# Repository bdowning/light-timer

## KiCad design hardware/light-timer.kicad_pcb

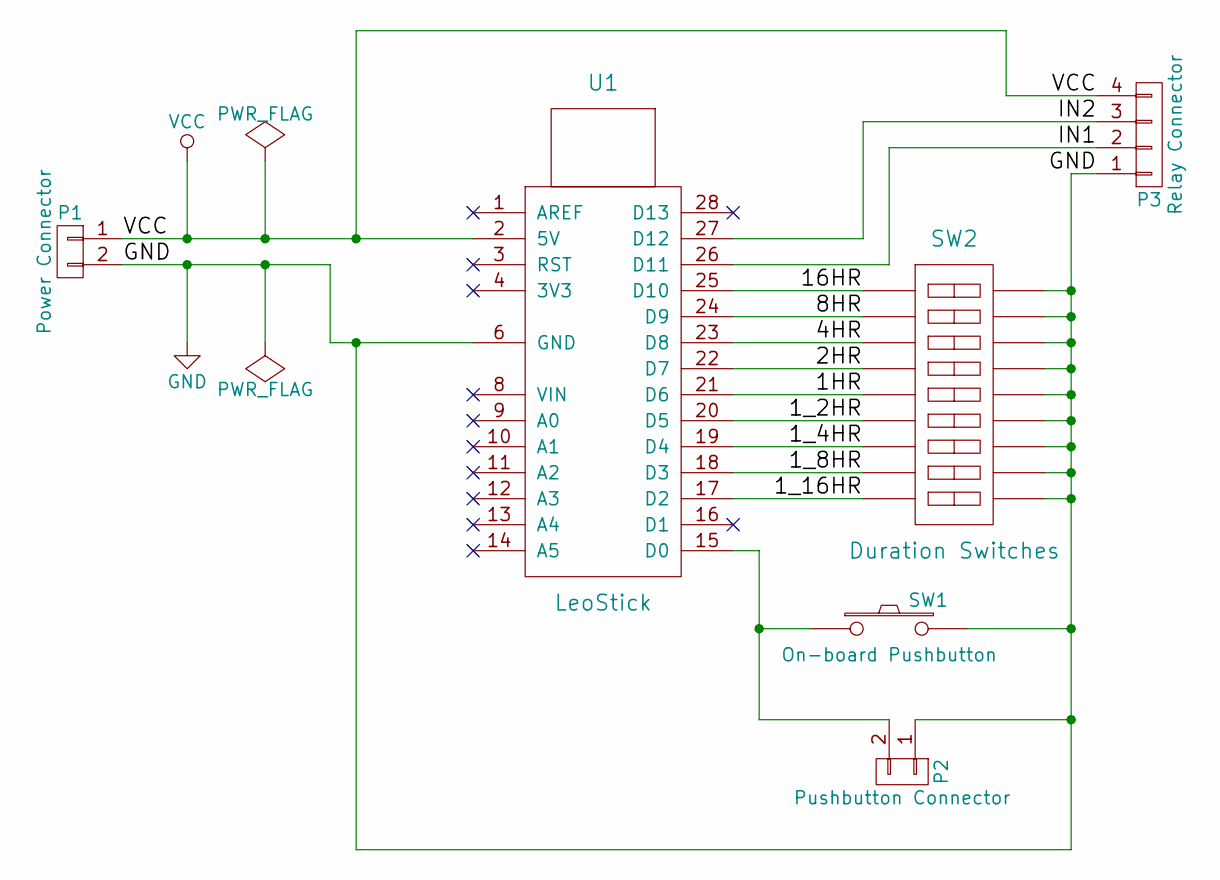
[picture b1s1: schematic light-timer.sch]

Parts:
P1: Power Connector; Socket_Strip_Straight_1x02
P2: Pushbutton Connector; Socket_Strip_Straight_1x02
P3: Relay Connector; Socket_Strip_Straight_1x04
SW1: On-board Pushbutton; SW_PUSH-12mm
SW2: Duration Switches; DIP-18_W7.62mm
U1: LeoStick; DIP-28_W15.24mm

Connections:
/1HR: SW2.5, U1.21 (D6)
/1_2HR: SW2.6, U1.20 (D5)
/1_4HR: SW2.7, U1.19 (D4)
/1_8HR: SW2.8, U1.18 (D3)
/1_16HR: SW2.9, U1.17 (D2)
/2HR: SW2.4, U1.22 (D7)
/4HR: SW2.3, U1.23 (D8)
/8HR: SW2.2, U1.24 (D9)
/16HR: SW2.1, U1.25 (D10)
/IN1: P3.2, U1.26 (D11)
/IN2: P3.3, U1.27 (D12)
GND: P1.2, P2.1, P3.1, SW1.2, SW2.10, SW2.11, SW2.12, SW2.13, SW2.14, SW2.15, SW2.16, SW2.17, SW2.18, U1.6 (GND)
unnamed: P2.2, SW1.1, U1.15 (D0)
VCC: P1.1, P3.4, U1.2 (5V)

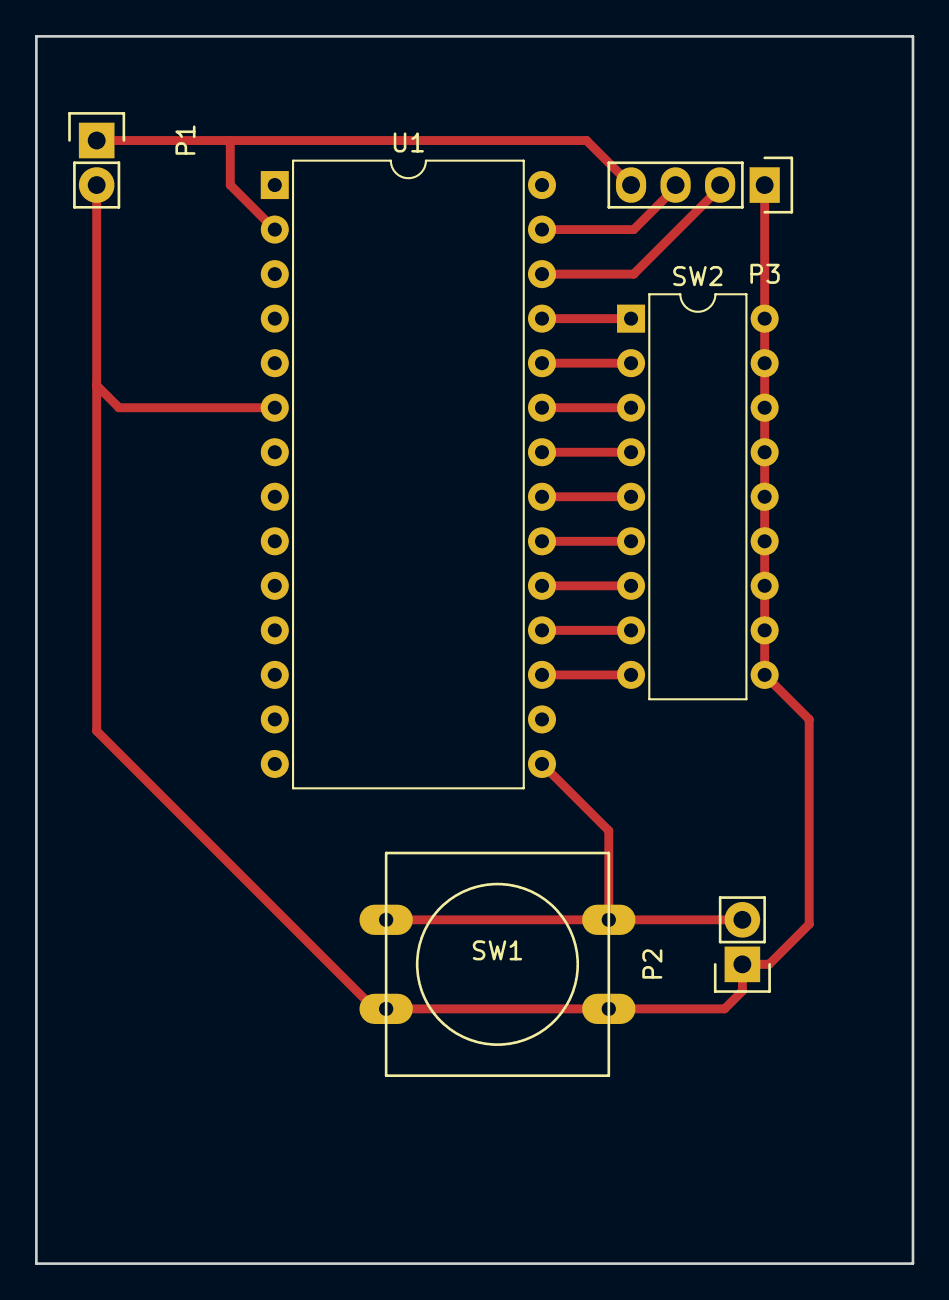
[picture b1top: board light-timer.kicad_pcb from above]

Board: 4 copper layers, 50.0 x 70.0 mm, 6 parts (0 on the bottom side), 14 nets.

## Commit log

2016-12-29 Silly light timer thing
2016-12-30 Add duration DIP switches, board layout
2016-12-30 Letter size schematics, PDF
